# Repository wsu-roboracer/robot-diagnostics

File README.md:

# Robot Diagnostics

A live health dashboard for Weber State University's **RoboRacer** (F1TENTH) cars. It runs on the car and opens in any browser on the same Wi-Fi, laptop or phone. In one screen it answers **"can I drive?"** and, when the answer is no, **"what is wrong?"**. It can also drive the car, with an emergency stop that works for everyone.

| Overview | Drive | Advanced |
|---|---|---|
|  |  |  |
| Battery, computer, subsystems, ROS graph, camera, LiDAR | Drive from the browser: camera, LiDAR radar, keys or thumb sticks | Every warning, worst first, and the detail behind it |

## Why it exists

When a RoboRacer misbehaves, the cause can be anywhere: a ROS node that did not start, a flat battery, a lost Wi-Fi link, an unplugged LiDAR, a controller that will not pair. Finding it meant checking each part by hand, in a terminal. The dashboard brings all of it onto one screen, graded in plain colours, so anyone using the cars (students in labs, instructors setting them up, developers testing code) knows where to start.

Every part of the car reports one of four states: **Healthy**, **Degraded**, **Failed** or **Unknown**. Unknown means the dashboard cannot tell yet; it never means failed.

## What it does

- **Status at a glance.** One verdict for the whole car, which names what is wrong: *DEGRADED — LiDAR, Battery*.
- **Battery** voltage and an estimate of what is left, judged on lines agreed with the course instructor.
- **The robot's computer:** CPU, RAM, GPU, temperatures, Wi-Fi quality, the LiDAR's cable and Bluetooth.
- **Subsystems:** controller, motor controller (VESC), LiDAR, odometry, camera and control mode, each with what is wrong in words and often how to fix it.
- **ROS graph:** which of the 12 expected nodes run and whether the key topics are flowing. Topics that only publish while someone drives are not flagged as broken at rest.
- **Live camera and LiDAR.** The LiDAR has a radar view that tags the nearest objects and says when something is getting closer.
- **Driving** from the browser, with a dead-man, speed and steering limits, edge warning lights, a full-screen first-person view, and thumb sticks on a phone. The physical controller always has priority.
- **Autonomous runs** from the page: a set speed and steering (or full speed), started with a button or by holding R1 on the controller, with an indicator and a Stop for anything autonomous on the car.
- **Obstacle stop:** while anything drives the car forward through `/drive`, the car watches its LiDAR ahead and stops itself before it hits something.
- **Emergency stop** for everyone: this page, other dashboards, the controller and autonomous code.
- **Troubleshooting tools:** a "Needs attention" list, every raw reading from the car's own checks, live topic messages, a joystick check, and the ROS warning log.
- **Controller tab:** a PS4 controller drawn live from `/joy`, with what is pressed lit up, the sticks and triggers moving, and the deadman buttons checked.
- **Robot picker** for F1-WSU-1 to F1-WSU-12, phone layout, and light and dark modes.

## Quick start

### Open it

With the dashboard running on a car, open this from any device on the lab Wi-Fi:

```
http://192.168.1.202:8000/dashboard.html
```

Each car is at `192.168.1.200` plus its number: F1-WSU-1 is `.201`, F1-WSU-12 is `.212`. You can switch cars from the robot list in the page's top bar.

### Start it on a car

Copy the dashboard to the car once, then start it:

```bash
rsync -av ~/Desktop/robot-diagnostics/prototype/ f1-wsu-2@192.168.1.202:~/diag/
ssh f1-wsu-2@192.168.1.202
cd ~/diag && ./start_diagnostics.sh     # bringup, checks, rosbridge, web server, camera
```

`./start_diagnostics.sh --status` shows what is up and `--stop` stops it; `--help` lists the rest. On cars where the dashboard is part of bringup (`f1tenth_stack`), plain `bringup` starts it too. Both ways are in [docs/system-overview.md](docs/system-overview.md#running-it).

### Work on it from a laptop

No copying needed. Serve the page locally and point it at a running car:

```bash
cd prototype
python3 -m http.server 8000
# open http://localhost:8000/dashboard.html?url=ws://192.168.1.202:9090
```

### Run the checks

No robot needed:

```bash
node prototype/tests/run.mjs
```

It prints PASS or FAIL for each check: the LiDAR geometry, beam selection, the system list and banners (against the page's real code), and the self-tests of the two robot-side services.

## How it works

```mermaid
flowchart LR
  subgraph car["On the car"]
    stack["Drive stack<br/>VESC, LiDAR, odometry,<br/>controller, mux"]
    sd["system_diagnostics.py<br/>OS checks, emergency stop,<br/>drive watchdog"]
    rb["rosbridge<br/>port 9090"]
    cam["camera_http.py<br/>port 8082"]
    web["web server<br/>port 8000"]
    stack -- "ROS 2 topics" --> rb
    sd -- "/diagnostics" --> rb
  end
  web -- "the page" --> browser["Browser on a laptop<br/>or phone"]
  rb <-- "WebSocket" --> browser
  cam -- "MJPEG" --> browser
```

- The car serves a **plain web page**: HTML, CSS and JavaScript, no build step, no internet needed.
- The page talks to ROS through **rosbridge**, so the laptop or phone needs nothing installed.
- **`system_diagnostics.py`** reports what ROS does not know about (temperatures, memory, Wi-Fi, USB devices, the clock) as a normal ROS node on `/diagnostics`. It also runs the emergency stop and the drive watchdog.
- **`camera_http.py`** relays the camera to browsers, always sending the newest frame, so a weak link drops frames rather than falling behind.

Why each piece is built this way, and which file to change for each check, is in [docs/system-overview.md](docs/system-overview.md).

## Documentation

| Read this | To |
|---|---|
| [Overview guide](docs/guides/overview-tab.md) | Read the first page: every card, colour and threshold |
| [Drive guide](docs/guides/drive-tab.md) | Drive a car from the dashboard safely |
| [Advanced guide](docs/guides/advanced-tab.md) | Find out why something is wrong |
| [Controller guide](docs/guides/controller-tab.md) | See live what the car hears from the PS4 controller |
| [System overview](docs/system-overview.md) | Understand how it works, run it, and change any check |
| [Drive control design](docs/design/dashboard-drive-control.md) | See how a command gets from the browser to the motors, and every safety rule |
| [Emergency stop design](docs/design/emergency-stop.md) | See what the emergency stop does on the car |
| [docs/README.md](docs/README.md) | Browse everything else: decisions (ADRs), research, sprint reviews |

## Where things live

| Folder | What is in it |
|---|---|
| [`prototype/`](prototype/) | **The dashboard.** The page (`dashboard.html`, `css/`, `js/`), the robot-side services (`system_diagnostics.py`, `camera_http.py`), the start script, tools for checking a car, and `tests/`. Its [README](prototype/README.md) maps every file |
| [`docs/`](docs/) | User guides, the system overview, design docs, decisions (ADRs), research, sprint reviews. Its [README](docs/README.md) is the index |
| [`diagnostic-hardware/`](diagnostic-hardware/) | The physical indicator: the PCB hat's Gerbers, EasyEDA project and layouts |
| [`Engineering_Logs/`](Engineering_Logs/) | Team members' engineering logs |
| [`Images/`](Images/) | Screenshots used in the logs and earlier docs |
| [`.github/`](.github/) | The checks every pull request runs, and the pull request template |

The dashboard grew out of the ROS status prototype, which is why it lives in `prototype/`. That folder is the working dashboard.

## Requirements

- **On the car:** ROS 2 Humble with the F1TENTH stack, `rosbridge_server`, Python 3, and GStreamer for the camera. `start_diagnostics.sh` starts everything.
- **To view it:** any modern browser on the same network. Nothing to install.
- **To run the checks:** Node.js (the pull request checks use Node 20) and Python 3. No robot, ROS or browser needed.

## Contributing

- **Find the right file first.** [prototype/README.md](prototype/README.md) maps the scripts, and [prototype/css/README.md](prototype/css/README.md) maps the styles. Every threshold and the robot list are in `prototype/js/config.js`.
- **Run `node prototype/tests/run.mjs`** before opening a pull request. Pull requests run it automatically, along with a check that every link in the docs works.
- **Changed what the page looks like?** Update the matching guide in [`docs/guides/`](docs/guides/) and its screenshots.
- **Made a decision that is hard to reverse?** Record it as an ADR in [`docs/adr/`](docs/adr/).
- **New documents** go in the matching folder in `docs/`, with lowercase-dash names and a line in [docs/README.md](docs/README.md).

## Contributors

- Saman Chapagain
- Luke Peterson
- Darrin Bracken
- Alex Stapp

Weber State University. Engineering logs are in [`Engineering_Logs/`](Engineering_Logs/).

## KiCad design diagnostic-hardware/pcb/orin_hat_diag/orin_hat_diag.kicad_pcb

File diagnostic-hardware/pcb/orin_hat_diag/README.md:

# Orin Nano Diagnostics HAT (KiCad 10)

> **DRAFT (rev 0.1).** Don't order boards from these files yet. The board is fully routed and passes KiCad's design rules check, but it still needs a human review, and the standoff holes need checking against the car's chassis plate. See [Board status and open items](#board-status-and-open-items).

A board for the Jetson Orin Nano dev kit. It has 10 status LEDs, an 8×8 LED matrix for showing obstacles, six user buttons that software can assign to anything, and a small OLED screen (by default it shows the Orin's IP addresses when SW2 is pressed).

The board is **L-shaped** so that it plugs straight onto the Orin's 40-pin header (J12) without a ribbon cable, and stays clear of the CPU heatsink and fan. The idea comes from the student's sketch, `Images/PCB_Hat_Designs/Improved Hat Design (recommended layout).pdf`. The dimensions come from NVIDIA's carrier-board layout (see [Fitting it to the Orin](#fitting-it-to-the-orin)).

- **Strip:** 40 × 116 mm at x 46–86, 1 mm clear of the heatsink. It holds the OLED, the user buttons, the LEDs and the matrix. It overhangs the carrier's port edge by 7 mm, high above the plugs.
- **Arm:** 46 × 24.5 mm along the header band. It ends at y = 16.5, before the module starts at y = 17.2. J1 sits under it, over the header.
- **Ends:** both ends extend 8 mm past the carrier, so the standoff holes sit beside the carrier, not over it.
- **Open area:** the heatsink and fan sit in the open space inside the L, so the airflow isn't blocked.

| File | Contents |
|---|---|
| `orin_hat_diag.kicad_sch` | Main sheet: header, buttons, OLED header, LED data buffer, status LEDs |
| `led_matrix.kicad_sch` | The 8×8 obstacle matrix |
| `orin_hat_diag.kicad_pcb` | L-shaped board, 86 × 116 mm overall, 2 layers, fully routed |

Driver code: [`prototype/hat_leds.py`](../../../prototype/hat_leds.py) (LEDs, buttons) and [`prototype/hat_display.py`](../../../prototype/hat_display.py) (OLED). Skeletons: [`hat_status_leds.py`](../../../prototype/hat_status_leds.py) (`/diagnostics` onto the named status LEDs), [`hat_obstacle_matrix.py`](../../../prototype/hat_obstacle_matrix.py) (`/scan` onto the 8x8 matrix).

## Header pin assignments

Pin numbers are physical (BOARD) numbers on the Orin's 40-pin header. J1 plugs straight onto it, so J1 uses the same numbering.

| Pin | Orin function | HAT signal | Direction | Used for |
|---|---|---|---|---|
| 19 | SPI0_MOSI (`/dev/spidev0.0`) | `SPI0_MOSI` | Orin → HAT | LED data. Goes through a 74AHCT1G125 3.3 V→5 V buffer to D1 |
| 29 | GPIO01 | `BTN1` | HAT → Orin | User button SW1 (on the arm) |
| 15 | GPIO12 | `BTN2` | HAT → Orin | User button SW2 (button row, leftmost) |
| 13 | SPI1_SCK | `BTN3` | HAT → Orin | User button SW3 |
| 12 | I2S0_SCLK | `BTN4` | HAT → Orin | User button SW4 |
| 11 | UART1_RTS | `BTN5` | HAT → Orin | User button SW5 |
| 7 | GPIO09 | `BTN6` | HAT → Orin | User button SW6 (button row, rightmost) |
| 3 | I2C7_SDA (`/dev/i2c-7`) | `I2C7_SDA` | both | OLED data (J2 pin 4). The Orin has the pull-ups |
| 5 | I2C7_SCL | `I2C7_SCL` | Orin → HAT | OLED clock (J2 pin 3) |
| 2, 4 | 5 V | `+5V` | power | LEDs and the buffer |
| 1, 17 | 3.3 V | `+3V3` | power | Button pull-ups and the OLED |
| 6, 9, 14, 20, 25, 30, 34, 39 | GND | `GND` | — | |

The other pins are not connected.

Every button works the same way: active low, a 10k pull-up to 3.3 V, then a 1k + 100 nF RC debounce in front of the header pin. Read them with `hat_leds.button_pressed(n)` for n = 1–6 (`BUTTON_PINS` maps buttons to pins). The silkscreen prints each row button's header pin under it. Pins 13 and 12 are only GPIOs while the second SPI bus and I2S are left off in `jetson-io`.

## How the LEDs are driven

All 74 LEDs are WS2812B addressable RGB LEDs on **one data line**. They are individually controlled, not multiplexed or scanned:

- Each LED contains its own small driver chip that stores a 24-bit colour.
- The Orin sends the colours for the whole chain as one burst on pin 19. Each LED keeps the first colour it receives and passes the rest to the next LED.
- After the burst, every LED holds its colour until the next update. The Orin doesn't need to refresh them, and any LED can be set to any colour on its own.

So the code needs one SPI pin, and it addresses LEDs by their **position in the chain**:

| Chain index | Parts | What it is |
|---|---|---|
| 0–4 | D1–D5 (5050 size) | Status LEDs, top row. Named on the silkscreen (see below) |
| 5–9 | D6–D10 (5050 size) | Status LEDs, second row, numbered 5–9 on the silkscreen. Free to assign to a system |
| 10–73 | D101–D164 (2020 size) | Obstacle matrix. `index = 10 + row*8 + col`. Row 0 is the row marked **FRONT**, column 0 is on the left |

The top-row names come from issue #64. `hat_leds.py` accepts each name in place of its number (`STATUS_NAMES`):

| Index | LED | Silkscreen | Shows the state of |
|---|---|---|---|
| 0 | D1 | LiDAR | `urg_node`'s own diagnostics (names starting "urg_node") |
| 1 | D2 | Camera | "system: Camera" |
| 2 | D3 | Network | "system: Network" (the Orin's own link, not rosbridge clients) |
| 3 | D4 | VESC | "system: VESC device" |
| 4 | D5 | Gamepad | "system: Gamepad" |

```
          col 0  1  2  3  4  5  6  7          (FRONT)
row 0        10 11 12 13 14 15 16 17
row 1        18 19 20 21 22 23 24 25
  ...
row 7        66 67 68 69 70 71 72 73
```

```python
from hat_leds import HatLeds, GREEN, RED
leds = HatLeds(brightness=0.25)
leds.set_status("LiDAR", GREEN)  # same as set_status(0, GREEN)
leds.set_status(7, GREEN)        # second-row LEDs are still numbered
leds.set_matrix(0, 3, RED)       # obstacle ahead, slightly left of centre
leds.show()                      # nothing changes on the board until show()
```

## OLED screen

J2 is a 1×4 header for a **0.91" 128×32 SSD1306 I2C OLED module** (about 38 × 12 mm, a few dollars, address 0x3C). It solders straight onto J2 and lies across the top of the strip, over the space between the header and the button row.

- **Buy it separately; JLCPCB doesn't assemble it.** Any generic 0.91" 128×32 SSD1306 I2C module with a 4-pin 0.1" header works, for example [ProtoSupplies' white 0.91" module](https://protosupplies.com/product/oled-0-91-128x32-i2c-white-display/) or a DSD TECH 2-pack. Avoid versions with a PH2.0 cable socket (Waveshare) or a different board size (DFRobot DFR0648). Buy a spare; the glass cracks easily.
- **Check the module's pin order before soldering.** J2 is GND, VCC, SCL, SDA from the top, as printed next to it. Most modules match, but some swap GND and VCC.
- It draws about 10–20 mA from 3.3 V.
- `python3 prototype/hat_display.py --watch` shows the hostname and IPv4 addresses for 10 s each time SW2 is pressed, then blanks the screen so it doesn't burn in. `--show-ip` shows them once. If the text is upside down, add `--rotate 2`.
- Setup: `pip3 install luma.oled`, add yourself to the `i2c` group, then `i2cdetect -y -r 7` should show the module at `3c`.

## Orin setup (once)

1. `sudo /opt/nvidia/jetson-io/jetson-io.py`: enable **SPI1** (pins 19/21/23/24/26), then reboot. After the reboot, `/dev/spidev0.0` should exist.
2. `sudo apt install python3-spidev`
3. For the buttons: `sudo usermod -aG gpio $USER`, then log out and back in. `Jetson.GPIO` is preinstalled on JetPack.
4. `python3 prototype/hat_leds.py --demo`

## Power budget

Full white on all 74 LEDs draws roughly 3 A, which is more than the header's 5 V pins should supply. `hat_leds.py` scales colours down to stay under `CURRENT_LIMIT_MA` (1000 mA, **provisional**) and defaults to 25 % brightness. Confirm the dev kit's 5 V limit on pins 2/4 before raising this. If the board needs to be brighter, it needs its own 5 V input.

## Layout

**Arm** (over the header band):
- J1 on the underside, a female 2×20 socket.
- On top, below the header pins: user button SW1 with its pull-up and debounce parts (R1, C1, R2), and the LED data buffer U1 with R3, R4 and C3.

**Strip** (beside the fan), from the top:
1. The OLED header J2 at the right edge; the module covers the strip from the header down to the buttons.
2. User buttons SW2–SW6 in one row at 7.6 mm pitch (six don't fit across the 40 mm strip), labelled SW2–SW6 above. All six buttons are 5.1 × 5.1 mm SMD tactile switches (XKB TS-1187A, LCSC C318884), so JLCPCB places them. SW2–SW6 are turned 90° so their pads run up and down, leaving about 2 mm between neighbours. Under each: its series resistor, debounce cap and pull-up (R10–R14, C4–C8, R5–R9), and the header pin it reads on.
3. Status LEDs in two rows of five: LiDAR, Camera, Network, VESC, Gamepad on top, then 5–9.
4. The 8×8 matrix at 4.5 mm pitch, with **FRONT** marked above row 0.
5. The 5 V bulk capacitor C2, below the matrix.

All the surface-mount parts are on top, so the board can be assembled in one pass. J1 is the only part on the underside. The underside silkscreen credits the team: Weber State University 2026, Alex Stapp, Luke Peterson, Saman Chapagain, Darrin Bracken and Scott Hadzik.

## Fitting it to the Orin

All positions here come from NVIDIA's carrier-board layout (`P3768_A04` in the *Jetson Orin Nano Developer Kit Carrier Board Reference Design Files*, A04, 2023-03-20). They're given in the HAT's frame: the origin is the carrier corner at the pin-39/40 end of the header, x runs along the header, and y runs toward the far edge. NVIDIA's own coordinates convert with x = 62 − y_nv and y = 96 − x_nv.

- **Header (J12):** pin 1 is at (57.13, 2.73) mm and pin 40 at (8.87, 5.27) mm. The odd row is on the board edge. J1 is placed on exactly these points, and the underside silkscreen marks pin 1. The student's sketch had pin 1 about 3 mm too far from the edge.
- **Module, heatsink and fan:** the module (69.6 × 45 mm) covers about x 0–45, y 17–87. That's 6 mm wider than the sketch shows, so the strip starts at x = 46 to stay clear of it.
- **Under the strip:** the USB 3 ports, RJ45 and USB connector run along x ≈ 66–79. They're the reason for the >25 mm height.
- **Mounting holes: the carrier has none free for a HAT.** It only has the module's two M2.5 holes at (3.5, 20.2) and (3.5, 83.8), which are under the heatsink, and three M3 nuts for the M.2 cards, on the underside. The one nut under the HAT, MEC3 at (46.5, 13.7), holds the SSD. **So the HAT stands on M2.5 standoffs down to the car's chassis plate, beside the carrier.** There are **three** standoffs. H1 (4, −4.5) and H2 (82, −4.5) are past the header-side edge, and H4 (82, 104.5) is past the far edge, at the bottom of the strip. A 5 mm hex standoff at each hole clears the carrier outline by 1.6–2.5 mm, and the nearest port is 14 mm away. With J1 on the header also holding the top edge, three points support the board. There's no H3: a fourth hole at the bottom-left of the strip didn't fit next to the camera connector J21.
- **Height:** a socket on the Orin's header gives only about 8.5 mm. To reach the >25 mm needed to clear the ports, stack 40-pin GPIO **stacking risers** (Raspberry Pi style extenders) between the Orin header and J1. Size the standoffs so that the HAT sits level at the height the risers set. The standoffs stand on the chassis plate, not on the carrier, so allow for the carrier's own mounting height when choosing them.

The `User.Comments` layer in the PCB draws the carrier underneath: its outline, the module area, the holes and the connectors.

## Routing

2 layers, 0.2 mm signal tracks, 0.3 mm power stubs, 0.6/0.3 mm vias.

- **Top (F.Cu): a +5V copper fill** over the whole board. The header's +5V pins and every +5V pad join it directly. Each LED's VDD pad also has a short track to its decoupling cap.
- **Bottom (B.Cu): a GND copper fill.** Every top-side GND pad has a short track to a via into it. J1 pins 20 and 30 have short bottom tracks, because there's no room for thermal spokes between neighbouring header pins.
- **LED data chain:** each LED connects to the next with a short top-layer track. The long jumps run on the bottom layer so they don't split the +5V fill: each matrix row's end back to the next row's start, D5→D6, and D10→D101. The chain starts at U1 in the arm and runs down the strip's left edge to D1.
- **User buttons SW2–SW6:** each header pin leaves the header on the bottom layer through the gaps in the inner row of pins, runs along the arm at y 9.5–15.5, then drops down the middle of its button to a via at the series resistor. On top, each switch's two pin-1 pads are joined and jog to the pull-up track. Its two GND pads are joined and drop through one via to the bottom fill. Their +3V3 comes from pin 1 along the top edge and down the strip's right edge on top, then along a bottom-layer bus under the pull-ups. J1 pins 6 and 14 get short bottom GND tracks, like pins 20 and 30.
- **I2C7 to the OLED:** pins 3 and 5 drop through the gaps beside pins 2 and 4 on the bottom layer, run right above the button tracks, and hop to the top layer just before J2. The hop keeps the bottom ground fill open down the strip's right edge, which is the only link between the fill over the arm and the rest of it. J2's VCC has a short top track to the +3V3 rail.
- **Arm signals** run on top, between the header pins:
  - SPI0_MOSI from pin 19 to U1 and R4;
  - BTN1 from pin 29 to R2;
  - the button's RC network.
- **+3V3:** pins 1 and 17 are joined on top, above the header. Pin 17 then runs on the bottom layer down through the gap between pins 18 and 20, and on to R1.
- **The status-LED caps (C11–C20) are rotated 180°**, so each cap's +5V pad faces its LED's VDD pad.

**Things to look at in review:**
- **+5V fill:** inside the matrix it reaches the LEDs through about 1 mm bands between rows and along the matrix sides. That's adequate for the 1 A software current limit. If you raise the limit, check those bands.
- **Bottom ground fill:** the long data jumps cut it into strips, which join at the matrix edges.
- **Refill before reviewing:** after editing, press **B** in KiCad to refill both fills before you run the board check.

## Board status and open items

- [ ] **Check H1, H2 and H4 against the chassis plate.** The standoffs go to the plate beside the carrier. Confirm the plate is solid at those three points, and drill or tap it as needed.
- [ ] Measure the USB/Ethernet stack height to fix the riser height.
- [ ] With the dev kit on the car, confirm the arm stays out of the fan area and the board doesn't block the fan's airflow.
- [x] Route the board (see [Routing](#routing)). The board check finds 0 violations and 0 unconnected items, and the board matches the schematic.
- [ ] Review the routing in KiCad before ordering, especially the +5V fill's narrow paths through the matrix (see [Routing](#routing)).
- [ ] Buy a 0.91" OLED module and check its size and pin order against J2 (outline on the `F.Fab` layer).
- [ ] Check the button row's height against whatever sits above the HAT (TS-1187A switches, 1.5 mm tall). The OLED module sits above the button row, not over it, but check that a finger can still reach the low buttons past it.
- [ ] Hardware bring-up: scope pin 19 and check the line idles low between frames. The driver sends a low byte first in case it doesn't.

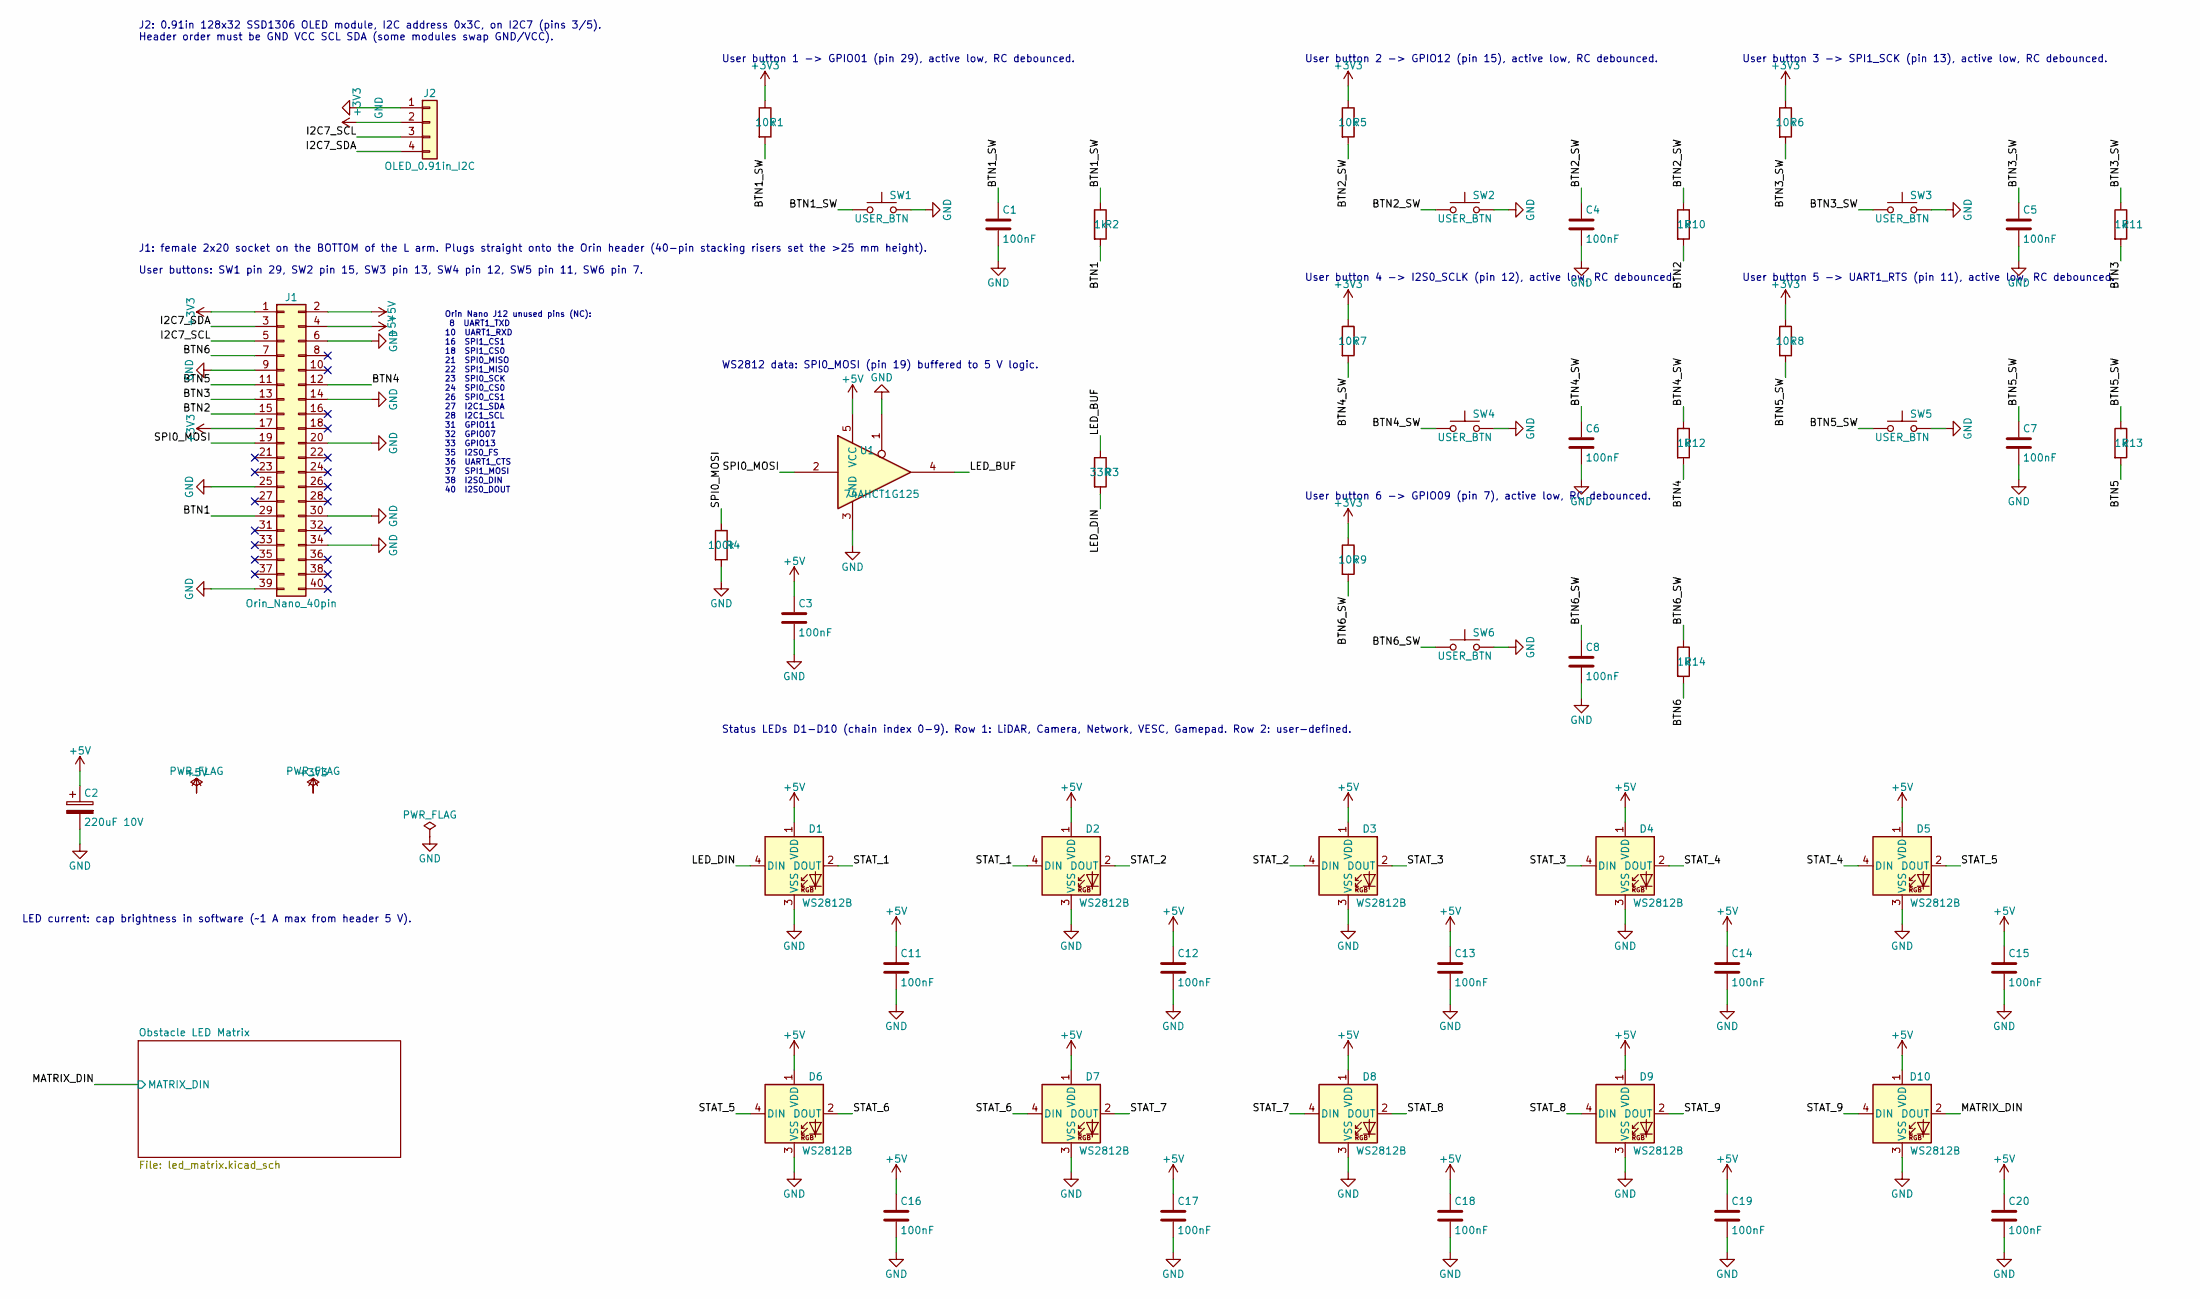
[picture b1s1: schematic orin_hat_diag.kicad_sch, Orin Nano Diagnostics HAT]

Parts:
C1, C3, C4, C5, C6, C7, C8, C11, C12, C13, C14, C15, C16, C17, C18, C19, C20: 100nF; C_0603_1608Metric
C2: 220uF 10V; CP_Elec_6.3x7.7
D1, D2, D3, D4, D5, D6, D7, D8, D9, D10: WS2812B; LED_WS2812B_PLCC4_5.0x5.0mm_P3.2mm
J1: Orin_Nano_40pin; PinSocket_2x20_P2.54mm_Vertical
J2: OLED_0.91in_I2C; PinHeader_1x04_P2.54mm_Vertical
R1, R5, R6, R7, R8, R9: 10k; R_0603_1608Metric
R2, R10, R11, R12, R13, R14: 1k; R_0603_1608Metric
R3: 33R; R_0603_1608Metric
R4: 100k; R_0603_1608Metric
SW1, SW2, SW3, SW4, SW5, SW6: USER_BTN; SW_Push_1P1T_XKB_TS-1187A
U1: 74AHCT1G125; SOT-23-5

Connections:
+3V3: J1.1, J1.17, J2.2, R1.1, R5.1, R6.1, R7.1, R8.1, R9.1
+5V: C2.1, C3.1, C11.1, C12.1, C13.1, C14.1, C15.1, C16.1, C17.1, C18.1, C19.1, C20.1, D1.1 (VDD), D2.1 (VDD), D3.1 (VDD), D4.1 (VDD), D5.1 (VDD), D6.1 (VDD), D7.1 (VDD), D8.1 (VDD), D9.1 (VDD), D10.1 (VDD), J1.2, J1.4, U1.5 (VCC); also elsewhere on the board
/BTN1: J1.29, R2.2
/BTN1_SW: C1.1, R1.2, R2.1, SW1.1
/BTN2: J1.15, R10.2
/BTN2_SW: C4.1, R5.2, R10.1, SW2.1
/BTN3: J1.13, R11.2
/BTN3_SW: C5.1, R6.2, R11.1, SW3.1
/BTN4: J1.12, R12.2
/BTN4_SW: C6.1, R7.2, R12.1, SW4.1
/BTN5: J1.11, R13.2
/BTN5_SW: C7.1, R8.2, R13.1, SW5.1
/BTN6: J1.7, R14.2
/BTN6_SW: C8.1, R9.2, R14.1, SW6.1
/I2C7_SCL: J1.5, J2.3
/I2C7_SDA: J1.3, J2.4
/LED_BUF: R3.1, U1.4
/LED_DIN: D1.4 (DIN), R3.2
/MATRIX_DIN: D10.2 (DOUT); also elsewhere on the board
/SPI0_MOSI: J1.19, R4.1, U1.2
/STAT_1: D1.2 (DOUT), D2.4 (DIN)
/STAT_2: D2.2 (DOUT), D3.4 (DIN)
/STAT_3: D3.2 (DOUT), D4.4 (DIN)
/STAT_4: D4.2 (DOUT), D5.4 (DIN)
/STAT_5: D5.2 (DOUT), D6.4 (DIN)
/STAT_6: D6.2 (DOUT), D7.4 (DIN)
/STAT_7: D7.2 (DOUT), D8.4 (DIN)
/STAT_8: D8.2 (DOUT), D9.4 (DIN)
/STAT_9: D9.2 (DOUT), D10.4 (DIN)
GND: C1.2, C2.2, C3.2, C4.2, C5.2, C6.2, C7.2, C8.2, C11.2, C12.2, C13.2, C14.2, C15.2, C16.2, C17.2, C18.2, C19.2, C20.2, D1.3 (VSS), D2.3 (VSS), D3.3 (VSS), D4.3 (VSS), D5.3 (VSS), D6.3 (VSS), D7.3 (VSS), D8.3 (VSS), D9.3 (VSS), D10.3 (VSS), J1.6, J1.9, J1.14, J1.20, J1.25, J1.30, J1.34, J1.39, J2.1, R4.2, SW1.2, SW2.2, SW3.2, SW4.2, SW5.2, SW6.2, U1.1, U1.3 (GND); also elsewhere on the board

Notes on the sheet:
J1: female 2x20 socket on the BOTTOM of the L arm. Plugs straight onto the Orin header (40-pin stacking risers set the >25 mm height).
User buttons: SW1 pin 29, SW2 pin 15, SW3 pin 13, SW4 pin 12, SW5 pin 11, SW6 pin 7.
Orin Nano J12 unused pins (NC): 8 UART1_TXD 10 UART1_RXD 16 SPI1_CS1 18 SPI1_CS0 21 SPI0_MISO 22 SPI1_MISO 23 SPI0_SCK 24 SPI0_CS0 26 SPI0_CS1 27 I2C1_SDA 28 I2C1_SCL 31 GPIO11 32 GPIO07 33 GPIO13 35 I2S0_FS 36 UART1_CTS 37 SPI1_MOSI 38 I2S0_DIN 40 I2S0_DOUT
LED current: cap brightness in software (~1 A max from header 5 V).
User button 1 -> GPIO01 (pin 29), active low, RC debounced.
WS2812 data: SPI0_MOSI (pin 19) buffered to 5 V logic.
Status LEDs D1-D10 (chain index 0-9). Row 1: LiDAR, Camera, Network, VESC, Gamepad. Row 2: user-defined.
User button 2 -> GPIO12 (pin 15), active low, RC debounced.
User button 3 -> SPI1_SCK (pin 13), active low, RC debounced.
User button 4 -> I2S0_SCLK (pin 12), active low, RC debounced.
User button 5 -> UART1_RTS (pin 11), active low, RC debounced.
User button 6 -> GPIO09 (pin 7), active low, RC debounced.
J2: 0.91in 128x32 SSD1306 OLED module, I2C address 0x3C, on I2C7 (pins 3/5). Header order must be GND VCC SCL SDA (some modules swap GND/VCC).

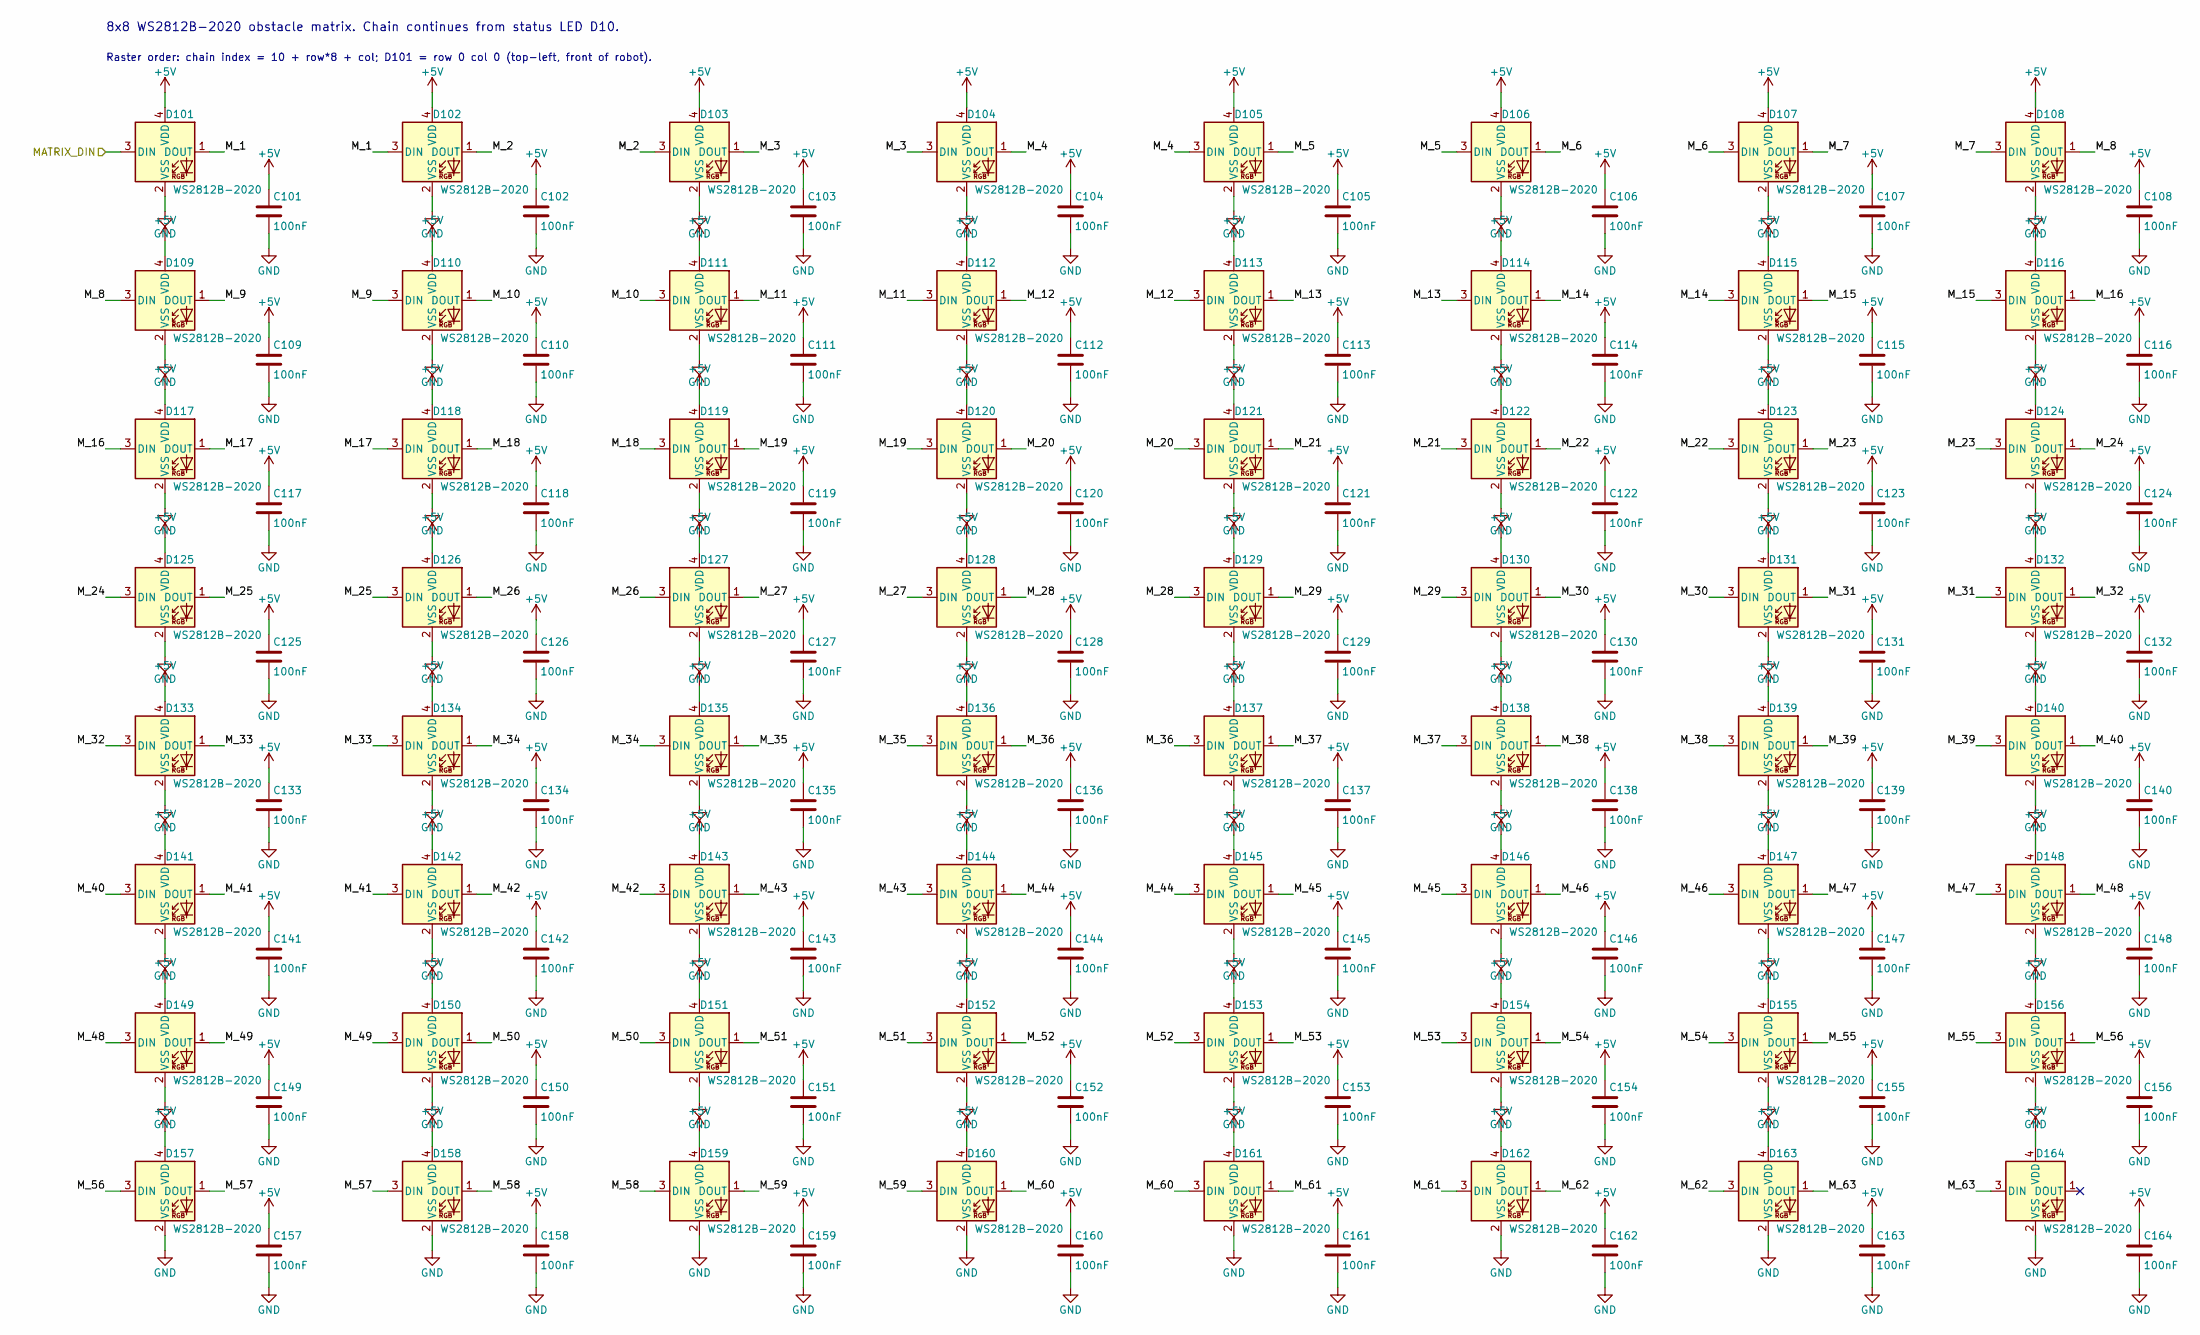
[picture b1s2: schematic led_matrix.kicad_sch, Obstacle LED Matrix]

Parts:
C101, C102, C103, C104, C105, C106, C107, C108, C109, C110, C111, C112, C113, C114, C115, C116, C117, C118, C119, C120, C121, C122, C123, C124, C125, C126, C127, C128, C129, C130, C131, C132, C133, C134, C135, C136, C137, C138, C139, C140, C141, C142, C143, C144, C145, C146, C147, C148, C149, C150, C151, C152, C153, C154, C155, C156, C157, C158, C159, C160, C161, C162, C163, C164: 100nF; C_0603_1608Metric
D101, D102, D103, D104, D105, D106, D107, D108, D109, D110, D111, D112, D113, D114, D115, D116, D117, D118, D119, D120, D121, D122, D123, D124, D125, D126, D127, D128, D129, D130, D131, D132, D133, D134, D135, D136, D137, D138, D139, D140, D141, D142, D143, D144, D145, D146, D147, D148, D149, D150, D151, D152, D153, D154, D155, D156, D157, D158, D159, D160, D161, D162, D163, D164: WS2812B-2020; LED_WS2812B-2020_PLCC4_2.0x2.0mm

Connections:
+5V: C101.1, C102.1, C103.1, C104.1, C105.1, C106.1, C107.1, C108.1, C109.1, C110.1, C111.1, C112.1, C113.1, C114.1, C115.1, C116.1, C117.1, C118.1, C119.1, C120.1, C121.1, C122.1, C123.1, C124.1, C125.1, C126.1, C127.1, C128.1, C129.1, C130.1, C131.1, C132.1, C133.1, C134.1, C135.1, C136.1, C137.1, C138.1, C139.1, C140.1, C141.1, C142.1, C143.1, C144.1, C145.1, C146.1, C147.1, C148.1, C149.1, C150.1, C151.1, C152.1, C153.1, C154.1, C155.1, C156.1, C157.1, C158.1, C159.1, C160.1, C161.1, C162.1, C163.1, C164.1, D101.4 (VDD), D102.4 (VDD), D103.4 (VDD), D104.4 (VDD), D105.4 (VDD), D106.4 (VDD), D107.4 (VDD), D108.4 (VDD), D109.4 (VDD), D110.4 (VDD), D111.4 (VDD), D112.4 (VDD), D113.4 (VDD), D114.4 (VDD), D115.4 (VDD), D116.4 (VDD), D117.4 (VDD), D118.4 (VDD), D119.4 (VDD), D120.4 (VDD), D121.4 (VDD), D122.4 (VDD), D123.4 (VDD), D124.4 (VDD), D125.4 (VDD), D126.4 (VDD), D127.4 (VDD), D128.4 (VDD), D129.4 (VDD), D130.4 (VDD), D131.4 (VDD), D132.4 (VDD), D133.4 (VDD), D134.4 (VDD), D135.4 (VDD), D136.4 (VDD), D137.4 (VDD), D138.4 (VDD), D139.4 (VDD), D140.4 (VDD), D141.4 (VDD), D142.4 (VDD), D143.4 (VDD), D144.4 (VDD), D145.4 (VDD), D146.4 (VDD), D147.4 (VDD), D148.4 (VDD), D149.4 (VDD), D150.4 (VDD), D151.4 (VDD), D152.4 (VDD), D153.4 (VDD), D154.4 (VDD), D155.4 (VDD), D156.4 (VDD), D157.4 (VDD), D158.4 (VDD), D159.4 (VDD), D160.4 (VDD), D161.4 (VDD), D162.4 (VDD), D163.4 (VDD), D164.4 (VDD); also elsewhere on the board
/MATRIX_DIN: D101.3 (DIN); also elsewhere on the board
/Obstacle LED Matrix/M_1: D101.1 (DOUT), D102.3 (DIN)
/Obstacle LED Matrix/M_2: D102.1 (DOUT), D103.3 (DIN)
/Obstacle LED Matrix/M_3: D103.1 (DOUT), D104.3 (DIN)
/Obstacle LED Matrix/M_4: D104.1 (DOUT), D105.3 (DIN)
/Obstacle LED Matrix/M_5: D105.1 (DOUT), D106.3 (DIN)
/Obstacle LED Matrix/M_6: D106.1 (DOUT), D107.3 (DIN)
/Obstacle LED Matrix/M_7: D107.1 (DOUT), D108.3 (DIN)
/Obstacle LED Matrix/M_8: D108.1 (DOUT), D109.3 (DIN)
/Obstacle LED Matrix/M_9: D109.1 (DOUT), D110.3 (DIN)
/Obstacle LED Matrix/M_10: D110.1 (DOUT), D111.3 (DIN)
/Obstacle LED Matrix/M_11: D111.1 (DOUT), D112.3 (DIN)
/Obstacle LED Matrix/M_12: D112.1 (DOUT), D113.3 (DIN)
/Obstacle LED Matrix/M_13: D113.1 (DOUT), D114.3 (DIN)
/Obstacle LED Matrix/M_14: D114.1 (DOUT), D115.3 (DIN)
/Obstacle LED Matrix/M_15: D115.1 (DOUT), D116.3 (DIN)
/Obstacle LED Matrix/M_16: D116.1 (DOUT), D117.3 (DIN)
/Obstacle LED Matrix/M_17: D117.1 (DOUT), D118.3 (DIN)
/Obstacle LED Matrix/M_18: D118.1 (DOUT), D119.3 (DIN)
/Obstacle LED Matrix/M_19: D119.1 (DOUT), D120.3 (DIN)
/Obstacle LED Matrix/M_20: D120.1 (DOUT), D121.3 (DIN)
/Obstacle LED Matrix/M_21: D121.1 (DOUT), D122.3 (DIN)
/Obstacle LED Matrix/M_22: D122.1 (DOUT), D123.3 (DIN)
/Obstacle LED Matrix/M_23: D123.1 (DOUT), D124.3 (DIN)
/Obstacle LED Matrix/M_24: D124.1 (DOUT), D125.3 (DIN)
/Obstacle LED Matrix/M_25: D125.1 (DOUT), D126.3 (DIN)
/Obstacle LED Matrix/M_26: D126.1 (DOUT), D127.3 (DIN)
/Obstacle LED Matrix/M_27: D127.1 (DOUT), D128.3 (DIN)
/Obstacle LED Matrix/M_28: D128.1 (DOUT), D129.3 (DIN)
/Obstacle LED Matrix/M_29: D129.1 (DOUT), D130.3 (DIN)
/Obstacle LED Matrix/M_30: D130.1 (DOUT), D131.3 (DIN)
/Obstacle LED Matrix/M_31: D131.1 (DOUT), D132.3 (DIN)
/Obstacle LED Matrix/M_32: D132.1 (DOUT), D133.3 (DIN)
/Obstacle LED Matrix/M_33: D133.1 (DOUT), D134.3 (DIN)
/Obstacle LED Matrix/M_34: D134.1 (DOUT), D135.3 (DIN)
/Obstacle LED Matrix/M_35: D135.1 (DOUT), D136.3 (DIN)
/Obstacle LED Matrix/M_36: D136.1 (DOUT), D137.3 (DIN)
/Obstacle LED Matrix/M_37: D137.1 (DOUT), D138.3 (DIN)
/Obstacle LED Matrix/M_38: D138.1 (DOUT), D139.3 (DIN)
/Obstacle LED Matrix/M_39: D139.1 (DOUT), D140.3 (DIN)
/Obstacle LED Matrix/M_40: D140.1 (DOUT), D141.3 (DIN)
/Obstacle LED Matrix/M_41: D141.1 (DOUT), D142.3 (DIN)
/Obstacle LED Matrix/M_42: D142.1 (DOUT), D143.3 (DIN)
/Obstacle LED Matrix/M_43: D143.1 (DOUT), D144.3 (DIN)
/Obstacle LED Matrix/M_44: D144.1 (DOUT), D145.3 (DIN)
/Obstacle LED Matrix/M_45: D145.1 (DOUT), D146.3 (DIN)
/Obstacle LED Matrix/M_46: D146.1 (DOUT), D147.3 (DIN)
/Obstacle LED Matrix/M_47: D147.1 (DOUT), D148.3 (DIN)
/Obstacle LED Matrix/M_48: D148.1 (DOUT), D149.3 (DIN)
/Obstacle LED Matrix/M_49: D149.1 (DOUT), D150.3 (DIN)
/Obstacle LED Matrix/M_50: D150.1 (DOUT), D151.3 (DIN)
/Obstacle LED Matrix/M_51: D151.1 (DOUT), D152.3 (DIN)
/Obstacle LED Matrix/M_52: D152.1 (DOUT), D153.3 (DIN)
/Obstacle LED Matrix/M_53: D153.1 (DOUT), D154.3 (DIN)
/Obstacle LED Matrix/M_54: D154.1 (DOUT), D155.3 (DIN)
/Obstacle LED Matrix/M_55: D155.1 (DOUT), D156.3 (DIN)
/Obstacle LED Matrix/M_56: D156.1 (DOUT), D157.3 (DIN)
/Obstacle LED Matrix/M_57: D157.1 (DOUT), D158.3 (DIN)
/Obstacle LED Matrix/M_58: D158.1 (DOUT), D159.3 (DIN)
/Obstacle LED Matrix/M_59: D159.1 (DOUT), D160.3 (DIN)
/Obstacle LED Matrix/M_60: D160.1 (DOUT), D161.3 (DIN)
/Obstacle LED Matrix/M_61: D161.1 (DOUT), D162.3 (DIN)
/Obstacle LED Matrix/M_62: D162.1 (DOUT), D163.3 (DIN)
/Obstacle LED Matrix/M_63: D163.1 (DOUT), D164.3 (DIN)
GND: C101.2, C102.2, C103.2, C104.2, C105.2, C106.2, C107.2, C108.2, C109.2, C110.2, C111.2, C112.2, C113.2, C114.2, C115.2, C116.2, C117.2, C118.2, C119.2, C120.2, C121.2, C122.2, C123.2, C124.2, C125.2, C126.2, C127.2, C128.2, C129.2, C130.2, C131.2, C132.2, C133.2, C134.2, C135.2, C136.2, C137.2, C138.2, C139.2, C140.2, C141.2, C142.2, C143.2, C144.2, C145.2, C146.2, C147.2, C148.2, C149.2, C150.2, C151.2, C152.2, C153.2, C154.2, C155.2, C156.2, C157.2, C158.2, C159.2, C160.2, C161.2, C162.2, C163.2, C164.2, D101.2 (VSS), D102.2 (VSS), D103.2 (VSS), D104.2 (VSS), D105.2 (VSS), D106.2 (VSS), D107.2 (VSS), D108.2 (VSS), D109.2 (VSS), D110.2 (VSS), D111.2 (VSS), D112.2 (VSS), D113.2 (VSS), D114.2 (VSS), D115.2 (VSS), D116.2 (VSS), D117.2 (VSS), D118.2 (VSS), D119.2 (VSS), D120.2 (VSS), D121.2 (VSS), D122.2 (VSS), D123.2 (VSS), D124.2 (VSS), D125.2 (VSS), D126.2 (VSS), D127.2 (VSS), D128.2 (VSS), D129.2 (VSS), D130.2 (VSS), D131.2 (VSS), D132.2 (VSS), D133.2 (VSS), D134.2 (VSS), D135.2 (VSS), D136.2 (VSS), D137.2 (VSS), D138.2 (VSS), D139.2 (VSS), D140.2 (VSS), D141.2 (VSS), D142.2 (VSS), D143.2 (VSS), D144.2 (VSS), D145.2 (VSS), D146.2 (VSS), D147.2 (VSS), D148.2 (VSS), D149.2 (VSS), D150.2 (VSS), D151.2 (VSS), D152.2 (VSS), D153.2 (VSS), D154.2 (VSS), D155.2 (VSS), D156.2 (VSS), D157.2 (VSS), D158.2 (VSS), D159.2 (VSS), D160.2 (VSS), D161.2 (VSS), D162.2 (VSS), D163.2 (VSS), D164.2 (VSS); also elsewhere on the board

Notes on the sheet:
8x8 WS2812B-2020 obstacle matrix. Chain continues from status LED D10.
Raster order: chain index = 10 + row*8 + col; D101 = row 0 col 0 (top-left, front of robot).

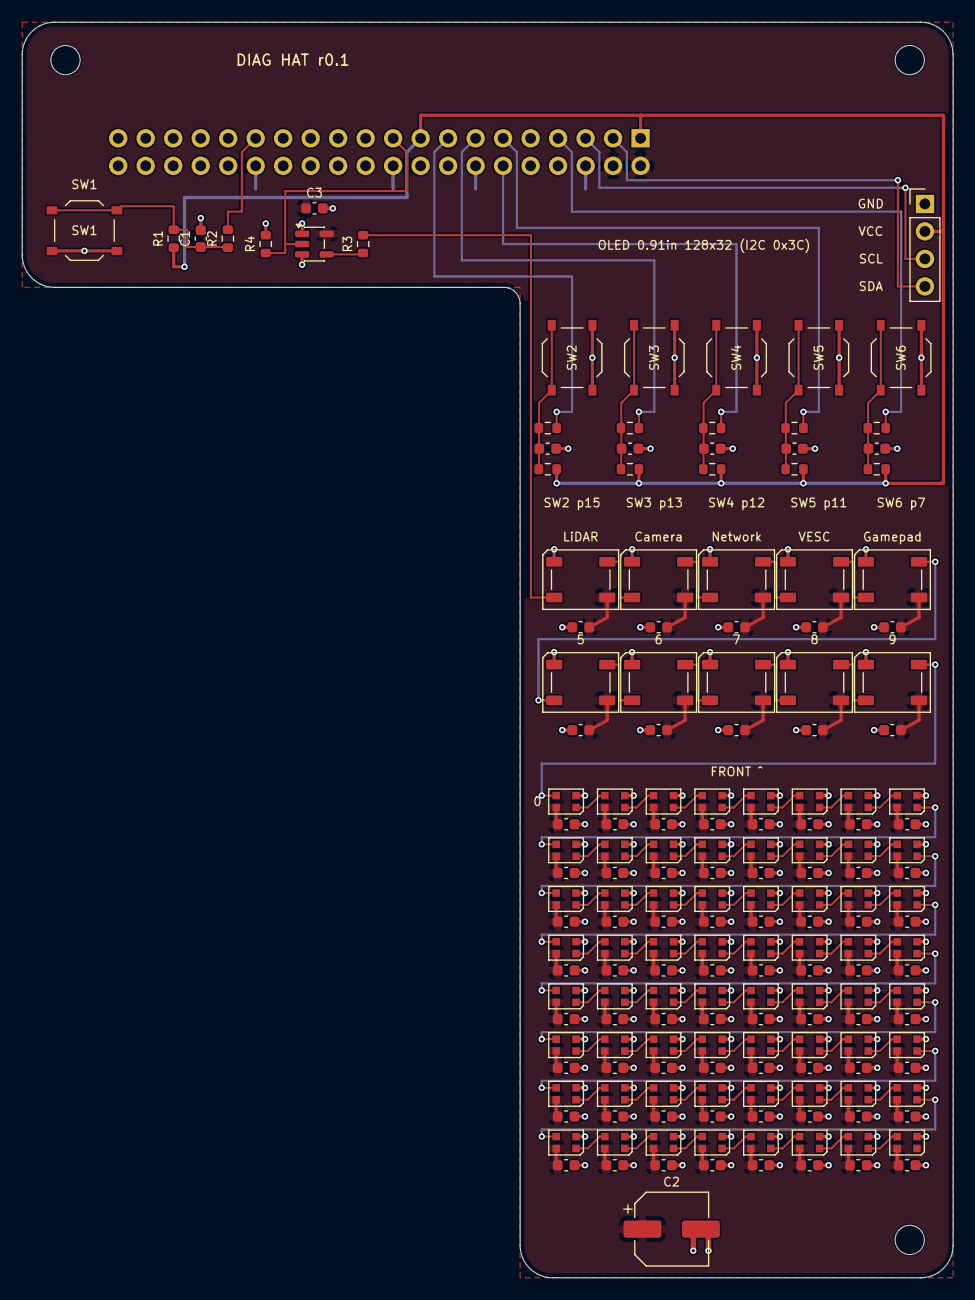
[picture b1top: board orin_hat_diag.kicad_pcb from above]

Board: 2 copper layers, 86.0 x 116.0 mm, 182 parts (1 on the bottom side), 93 nets.

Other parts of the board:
H1, H2, H4: MountingHole_2.7mm_M2.5

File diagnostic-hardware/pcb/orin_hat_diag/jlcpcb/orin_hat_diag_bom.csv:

Comment,Designator,Footprint,LCSC Part #
100k,R4,R_0603_1608Metric,C25803
100nF,"C1,C3,C4,C5,C6,C7,C8,C11,C12,C13,C14,C15,C16,C17,C18,C19,C20,C101,C102,C103,C104,C105,C106,C107,C108,C109,C110,C111,C112,C113,C114,C115,C116,C117,C118,C119,C120,C121,C122,C123,C124,C125,C126,C127,C128,C129,C130,C131,C132,C133,C134,C135,C136,C137,C138,C139,C140,C141,C142,C143,C144,C145,C146,C147,C148,C149,C150,C151,C152,C153,C154,C155,C156,C157,C158,C159,C160,C161,C162,C163,C164",C_0603_1608Metric,C14663
10k,"R1,R5,R6,R7,R8,R9",R_0603_1608Metric,C25804
1k,"R2,R10,R11,R12,R13,R14",R_0603_1608Metric,C21190
220uF 10V,C2,CP_Elec_6.3x7.7,C401650
33R,R3,R_0603_1608Metric,C23140
74AHCT1G125,U1,SOT-23-5,C12494
USER_BTN,"SW1,SW2,SW3,SW4,SW5,SW6",SW_Push_1P1T_XKB_TS-1187A,C318884
WS2812B,"D1,D2,D3,D4,D5,D6,D7,D8,D9,D10",LED_WS2812B_PLCC4_5.0x5.0mm_P3.2mm,C2843785
WS2812B-2020,"D101,D102,D103,D104,D105,D106,D107,D108,D109,D110,D111,D112,D113,D114,D115,D116,D117,D118,D119,D120,D121,D122,D123,D124,D125,D126,D127,D128,D129,D130,D131,D132,D133,D134,D135,D136,D137,D138,D139,D140,D141,D142,D143,D144,D145,D146,D147,D148,D149,D150,D151,D152,D153,D154,D155,D156,D157,D158,D159,D160,D161,D162,D163,D164",LED_WS2812B-2020_PLCC4_2.0x2.0mm,C5349955
